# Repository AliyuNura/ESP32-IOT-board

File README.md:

# ESP32-IOT-board
This is an esp32 board with pins to fit in 42mm breadboard in order to have a space to get connected to GPIO pins.

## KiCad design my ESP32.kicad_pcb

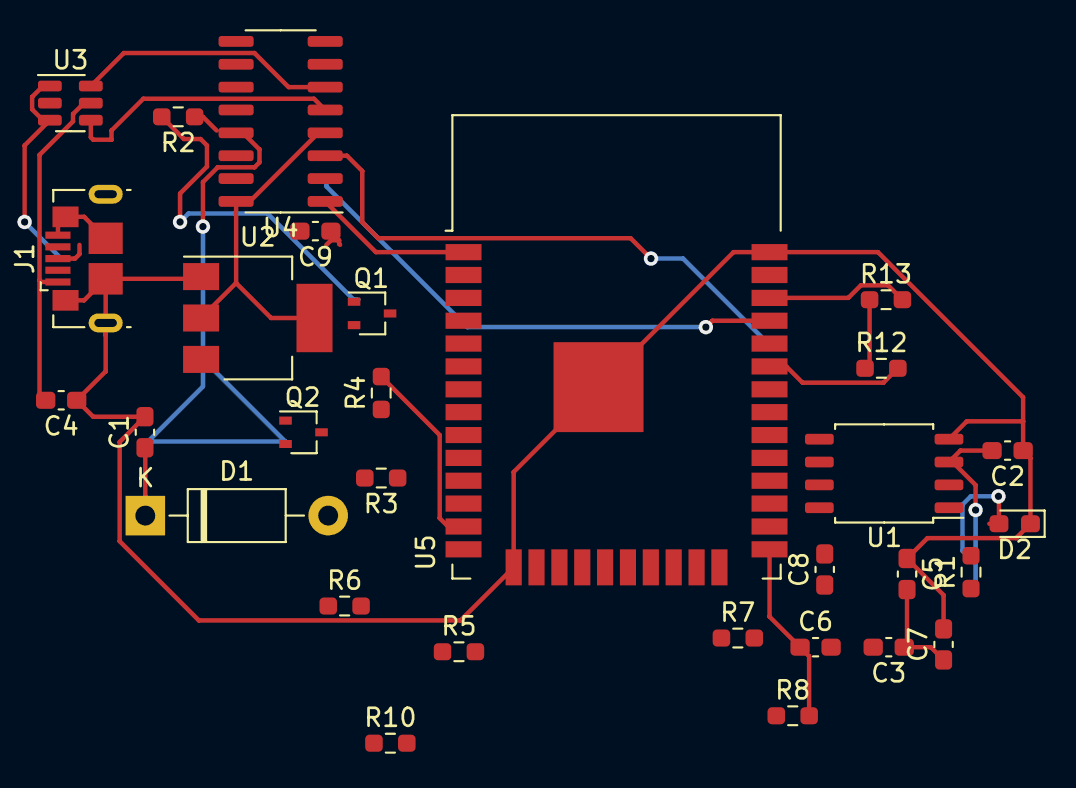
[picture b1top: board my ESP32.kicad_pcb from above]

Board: 2 copper layers, 30 parts (0 on the bottom side), 27 nets.

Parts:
C1, C3: 10uF; C_0603_1608Metric_Pad1.08x0.95mm_HandSolder
C2, C5: 0.1uF; C_0603_1608Metric_Pad1.08x0.95mm_HandSolder
C4: 100nF; C_0603_1608Metric_Pad1.08x0.95mm_HandSolder
C6, C9: 1nF/50V; C_0603_1608Metric_Pad1.08x0.95mm_HandSolder
C7: 1UF; C_0603_1608Metric_Pad1.08x0.95mm_HandSolder
C8: 100UF; C_0603_1608Metric_Pad1.08x0.95mm_HandSolder
D1: 1N5819; D_DO-41_SOD81_P10.16mm_Horizontal
D2: LED; LED_0603_1608Metric_Pad1.05x0.95mm_HandSolder
J1: USB_B_Micro; USB_Micro-B_GCT_USB3076-30-A
Q1, Q2: 2SC4213; SOT-323_SC-70
R1, R12, R13: 10K; R_0603_1608Metric_Pad0.98x0.95mm_HandSolder
R2, R3: 12K; R_0603_1608Metric_Pad0.98x0.95mm_HandSolder
R4, R5, R6, R7: 100; R_0603_1608Metric_Pad0.98x0.95mm_HandSolder
R8, R10: 220; R_0603_1608Metric_Pad0.98x0.95mm_HandSolder
U1: W25Q128JVS; SOIC-8_5.23x5.23mm_P1.27mm
U2: AMS1117-3.3; SOT-223-3_TabPin2
U3: USBLC6-2SC6; SOT-23-6
U4: CH340G; SOIC-16_3.9x9.9mm_P1.27mm
U5: ESP32-WROOM-32

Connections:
+3V3: C2.2, C3.1, C5.2, C7.1, C8.1, R1.1, U1.3 (IO2), U1.7 (IO3), U1.8 (VCC), U2.2 (VO), U4.4 (V3), U4.16 (VCC), U5.2 (VDD)
D+_IN: U3.4 (I/O2), U4.5 (UD+)
D+_OUT: J1.3 (D+), U3.1 (I/O1), U3.3 (I/O2)
D-_IN: U3.6 (I/O1), U4.6 (UD-)
DTR: Q2.2 (E), R2.1, U4.13 (~DTR)
EN: C9.1, Q1.3 (C), R10.2, U5.3 (EN)
GND: C1.2, C2.1, C3.2, C4.1, C5.1, C6.2, C7.2, C8.2, C9.2, D2.1 (K), J1.5 (GND), J1.6 (Shield), U1.4 (GND), U2.1 (GND), U3.2 (GND), U4.1 (GND), U5.1 (GND), U5.15 (GND), U5.38 (GND), U5.39 (GND)
I2C_SCL1: R13.2, U5.36 (IO22)
I2C_SDA1: R12.2, U5.33 (IO21)
IO0: C6.1, Q2.3 (C), R8.2, U5.25 (IO0)
MTCK: R6.2, U5.16 (IO13)
MTDI: R5.2, U5.14 (IO12)
MTDO: R7.2, U5.23 (IO15)
MTMS: R4.2, U5.13 (IO14)
unnamed: C1.1, D1.1 (K), U2.3 (VI)
unnamed: D2.2 (A), R1.2
unnamed: Q1.1 (B), R2.2
unnamed: Q2.1 (B), R3.2
unnamed: R12.1, R13.1
RST: Q1.2 (E), R3.1
RXD: U4.3 (RXD), U5.34 (RXD0/IO3)
SPI_CLK: U1.6 (CLK), U5.20 (SCK/CLK)
SPI_CS: U1.1 (~CS), U5.19 (SCS/CMD)
SPI_D0: U1.5 (DI(IO0)), U5.21 (SDO/SD0)
SPI_D1: U1.2 (DO(IO1)), U5.22 (SDI/SD1)
TXD: U4.2 (TXD), U5.35 (TXD0/IO1)
VBUS: C4.2, J1.1 (VBUS), U3.5 (VBUS)

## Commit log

2022-09-13 unfinished ESP32 design
